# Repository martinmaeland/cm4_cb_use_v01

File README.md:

# Command Module 4 Carrierboard Utksytningsenhet
This simple pcb will be used in a deployment unit (utskytningsenhet) for controlling several drones.

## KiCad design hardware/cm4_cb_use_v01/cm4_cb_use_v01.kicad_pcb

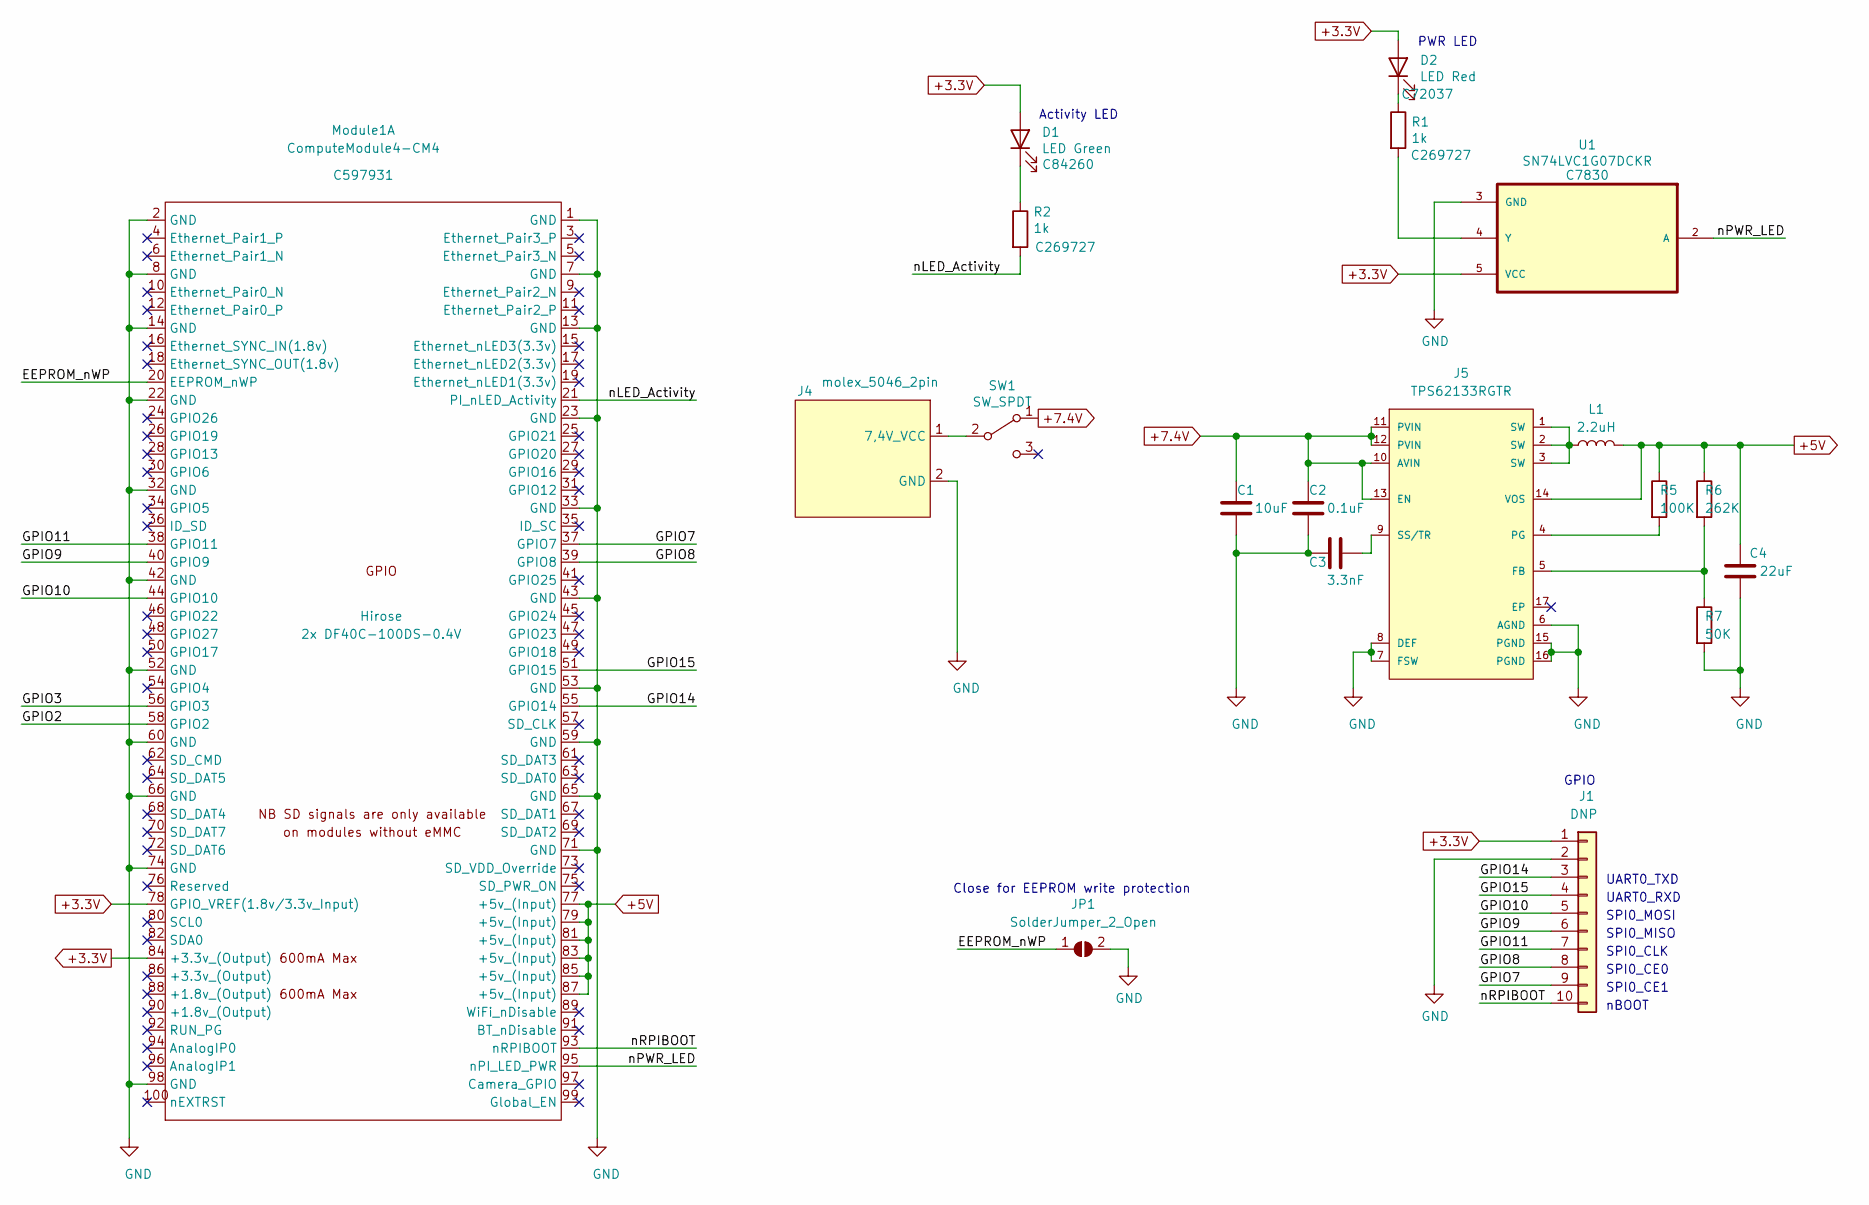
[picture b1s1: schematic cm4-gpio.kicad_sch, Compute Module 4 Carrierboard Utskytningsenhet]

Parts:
C1: 10uF; C_0805_2012Metric; MPN CL21A106KPFNNNE; LCSC PN C17024
C2: 0.1uF; C_0805_2012Metric; MPN CL21B104KBCNNNC; LCSC PN C1711
C3: 3.3nF; C_0805_2012Metric; MPN CL21B332KBANNNC; LCSC PN C53175
C4: 22uF; C_0805_2012Metric; MPN CL21C220JBANNNC; LCSC PN C1804
D1: LED Green; LED_0805_2012Metric; Part Description Green 525~537.5nm 0805 Light Emitting D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; LCSC C84260
D2: LED Red; LED_0805_2012Metric; Part Description Red 624~632nm 0805 Light Emitting Diode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; LCSC C72037
J1: DNP; PinHeader_1x10_P2.54mm_Vertical
J4: molex_5046_2pin; Molex_KK-254_AE-6410-02A_1x02_P2.54mm_Vertical
J5: TPS62133RGTR; Texas_Instruments-TPS62133RGTR-Manufacturer_Recommended; Rating Catalog
JP1: SolderJumper_2_Open; SolderJumper-2_P1.3mm_Open_RoundedPad1.0x1.5mm
L1: 2.2uH; L_0805_2012Metric; MPN SCMI201209U2R2KT; LCSC PN C479898
Module1: ComputeModule4-CM4; Raspberry-Pi-4-Compute-Module; MPN 2x DF40C-100DS-0.4V; Digi-Key_PN 2x H11615CT-ND
R1, R2: 1k; R_0805_2012Metric; MPN RMC08051K5%N; LCSC C269727
R5: 100K; R_0805_2012Metric; MPN AECR0805F100KK9; LCSC PN C328379
R6: 262K; R_0805_2012Metric
R7: 50K; R_0805_2012Metric
SW1: SW_SPDT; c&k_slide_switch_1101M2S3AQE2
U1: SN74LVC1G07DCKR; SOT65P210X110-5N; LCSC C7830

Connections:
+3.3V: D1.2 (A), D2.2 (A), J1.1, Module1.78 (GPIO_VREF(1.8v/3.3v_Input)), Module1.84 (+3.3v_(Output)), U1.5 (VCC)
+5V: C4.1, J5.14 (VOS), L1.2, Module1.77 (+5v_(Input)), Module1.79 (+5v_(Input)), Module1.81 (+5v_(Input)), Module1.83 (+5v_(Input)), Module1.85 (+5v_(Input)), Module1.87 (+5v_(Input)), R5.1, R6.1; also elsewhere on the board
+7.4V: C1.1, C2.1, J5.10 (AVIN), J5.11 (PVIN), J5.12 (PVIN), J5.13 (EN), SW1.1 (A)
/CM4 GPIO/EEPROM_nWP: JP1.1 (A), Module1.20 (EEPROM_nWP)
/CM4 GPIO/GPIO2: Module1.58 (GPIO2)
/CM4 GPIO/GPIO3: Module1.56 (GPIO3)
/CM4 GPIO/GPIO7: J1.9, Module1.37 (GPIO7)
/CM4 GPIO/GPIO8: J1.8, Module1.39 (GPIO8)
/CM4 GPIO/GPIO9: J1.6, Module1.40 (GPIO9)
/CM4 GPIO/GPIO10: J1.5, Module1.44 (GPIO10)
/CM4 GPIO/GPIO11: J1.7, Module1.38 (GPIO11)
/CM4 GPIO/GPIO14: J1.3, Module1.55 (GPIO14)
/CM4 GPIO/GPIO15: J1.4, Module1.51 (GPIO15)
/CM4 GPIO/nLED_Activity: Module1.21 (PI_nLED_Activity), R2.2
/CM4 GPIO/nPWR_LED: Module1.95 (nPI_LED_PWR), U1.2 (A)
/CM4 GPIO/nRPIBOOT: J1.10, Module1.93 (nRPIBOOT)
GND: C1.2, C2.2, C3.2, C4.2, J1.2, J4.2 (GND), J5.6 (AGND), J5.7 (FSW), J5.8 (DEF), J5.15 (PGND), J5.16 (PGND), JP1.2 (B), Module1.1 (GND), Module1.2 (GND), Module1.7 (GND), Module1.8 (GND), Module1.13 (GND), Module1.14 (GND), Module1.22 (GND), Module1.23 (GND), Module1.32 (GND), Module1.33 (GND), Module1.42 (GND), Module1.43 (GND), Module1.52 (GND), Module1.53 (GND), Module1.59 (GND), Module1.60 (GND), Module1.65 (GND), Module1.66 (GND), Module1.71 (GND), Module1.74 (GND), Module1.98 (GND), R7.2, U1.3 (GND); also elsewhere on the board
unnamed: C3.1, J5.9 (SS/TR)
unnamed: D1.1 (K), R2.1
unnamed: D2.1 (K), R1.1
unnamed: J4.1 (7,4V_VCC), SW1.2 (B)
unnamed: J5.1 (SW), J5.2 (SW), J5.3 (SW), L1.1
unnamed: J5.4 (PG), R5.2
unnamed: J5.5 (FB), R6.2, R7.1
unnamed: R1.2, U1.4 (Y)

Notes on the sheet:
Activity LED
Close for EEPROM write protection
PWR LED
GPIO
UART0_TXD
UART0_RXD
SPI0_MOSI
SPI0_MISO
SPI0_CLK
SPI0_CE0
SPI0_CE1
nBOOT

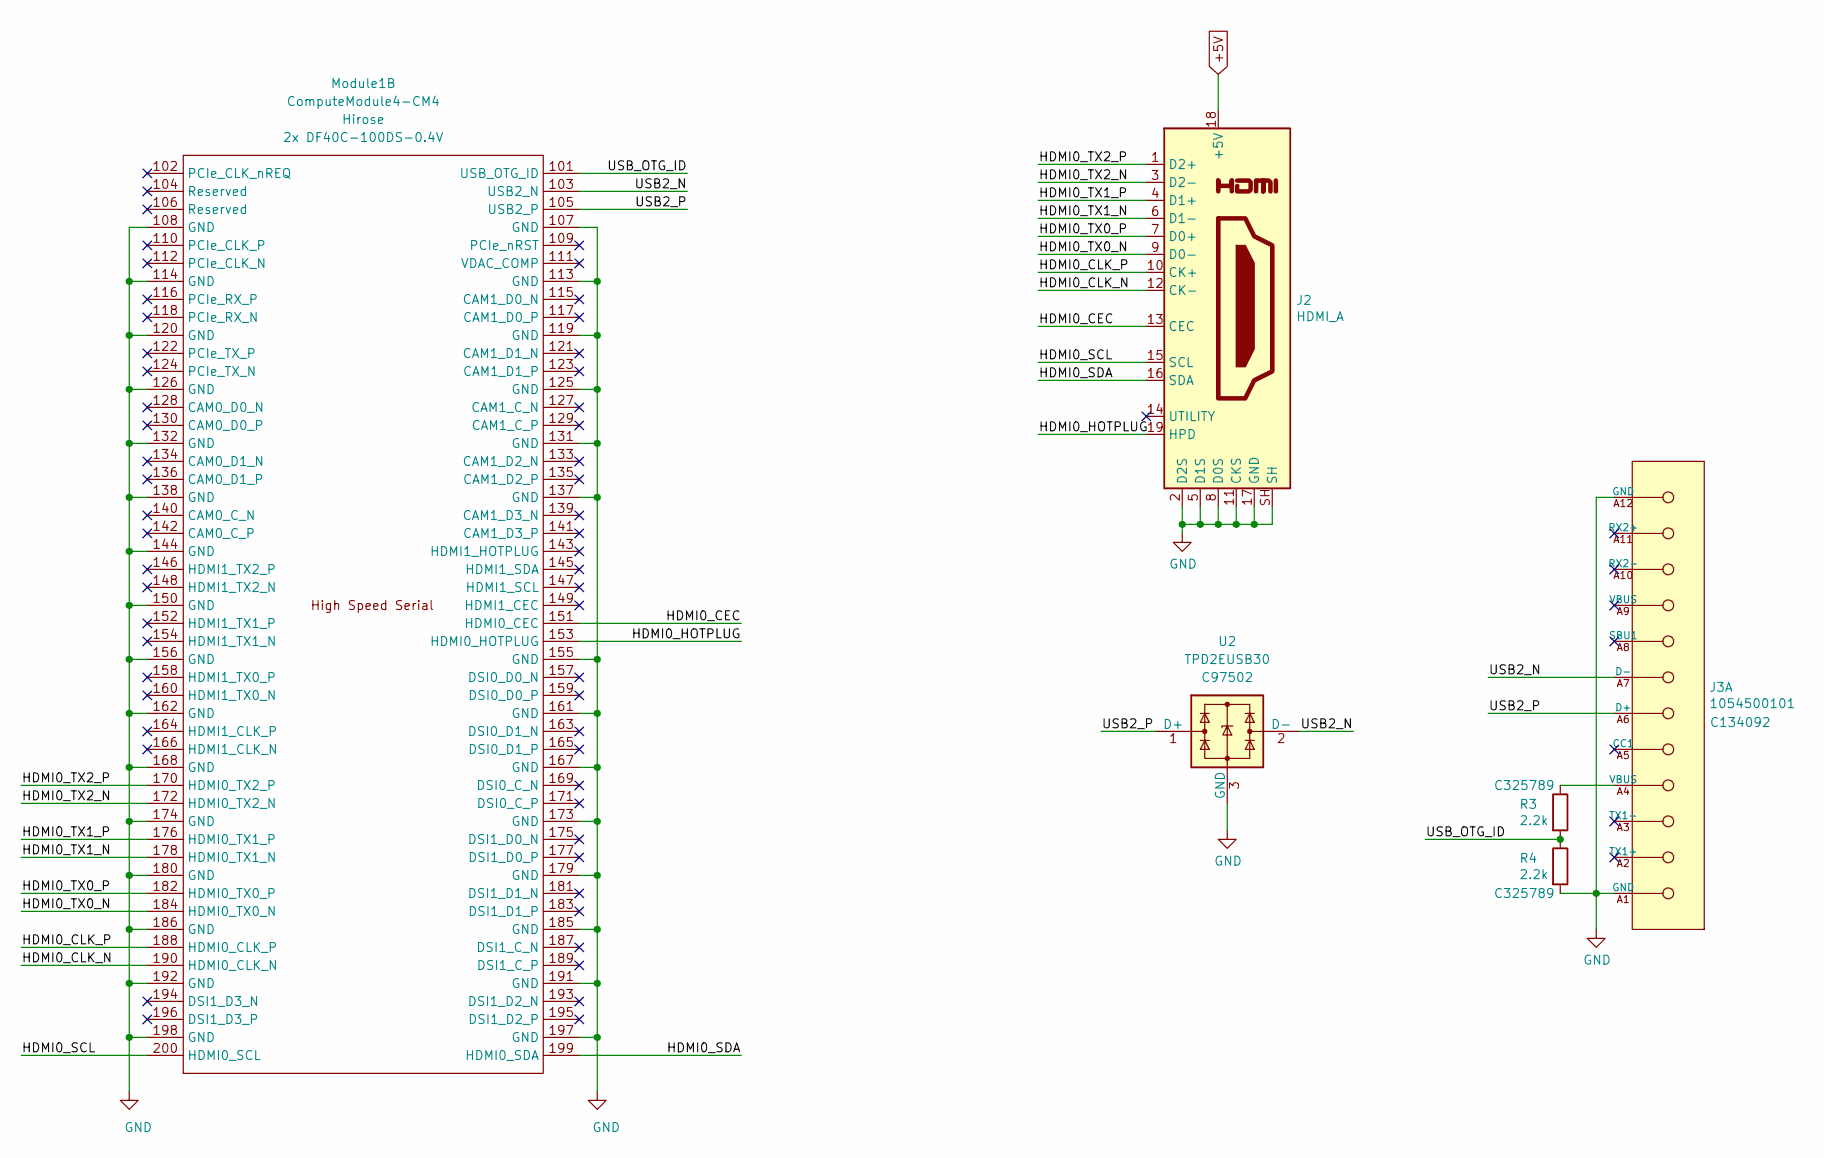
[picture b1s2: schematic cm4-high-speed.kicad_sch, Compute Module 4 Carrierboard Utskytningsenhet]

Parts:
J2: HDMI_A; molex_hdmi; LCSC C111617
J3: 1054500101; Molex-1054500101-MFG; current rating 0.25/1.25/5A; voltage rating 30V; mouser part number 538-105450-0101; digikey description CONN RCP USB3.1 TYPEC 24P SMD RA
Module1: ComputeModule4-CM4; Raspberry-Pi-4-Compute-Module; Digi-Key_PN 2x H11615CT-ND
R3, R4: 2.2k; R_0805_2012Metric; LCSC C325789
U2: TPD2EUSB30; Texas_DRT-3; MPN TPD2EUSB30DRTR; LCSC C97502

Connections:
+5V: J2.18 (+5V); also elsewhere on the board
/CM4 High Speed/HDMI0_CEC: J2.13 (CEC), Module1.151 (HDMI0_CEC)
/CM4 High Speed/HDMI0_CLK_N: J2.12 (CK-), Module1.190 (HDMI0_CLK_N)
/CM4 High Speed/HDMI0_CLK_P: J2.10 (CK+), Module1.188 (HDMI0_CLK_P)
/CM4 High Speed/HDMI0_HOTPLUG: J2.19 (HPD), Module1.153 (HDMI0_HOTPLUG)
/CM4 High Speed/HDMI0_SCL: J2.15 (SCL), Module1.200 (HDMI0_SCL)
/CM4 High Speed/HDMI0_SDA: J2.16 (SDA), Module1.199 (HDMI0_SDA)
/CM4 High Speed/HDMI0_TX0_N: J2.9 (D0-), Module1.184 (HDMI0_TX0_N)
/CM4 High Speed/HDMI0_TX0_P: J2.7 (D0+), Module1.182 (HDMI0_TX0_P)
/CM4 High Speed/HDMI0_TX1_N: J2.6 (D1-), Module1.178 (HDMI0_TX1_N)
/CM4 High Speed/HDMI0_TX1_P: J2.4 (D1+), Module1.176 (HDMI0_TX1_P)
/CM4 High Speed/HDMI0_TX2_N: J2.3 (D2-), Module1.172 (HDMI0_TX2_N)
/CM4 High Speed/HDMI0_TX2_P: J2.1 (D2+), Module1.170 (HDMI0_TX2_P)
/CM4 High Speed/USB2_N: J3.A7 (D-), Module1.103 (USB2_N), U2.2 (D-)
/CM4 High Speed/USB2_P: J3.A6 (D+), Module1.105 (USB2_P), U2.1 (D+)
/CM4 High Speed/USB_OTG_ID: Module1.101 (USB_OTG_ID), R3.2, R4.1
GND: J2.2 (D2S), J2.5 (D1S), J2.8 (D0S), J2.11 (CKS), J2.17 (GND), J2.SH, J3.A1 (GND), J3.A12 (GND), Module1.107 (GND), Module1.108 (GND), Module1.113 (GND), Module1.114 (GND), Module1.119 (GND), Module1.120 (GND), Module1.125 (GND), Module1.126 (GND), Module1.131 (GND), Module1.132 (GND), Module1.137 (GND), Module1.138 (GND), Module1.144 (GND), Module1.150 (GND), Module1.155 (GND), Module1.156 (GND), Module1.161 (GND), Module1.162 (GND), Module1.167 (GND), Module1.168 (GND), Module1.173 (GND), Module1.174 (GND), Module1.179 (GND), Module1.180 (GND), Module1.185 (GND), Module1.186 (GND), Module1.191 (GND), Module1.192 (GND), Module1.197 (GND), Module1.198 (GND), R4.2, U2.3 (GND); also elsewhere on the board
unnamed: J3.A4 (VBUS), R3.1

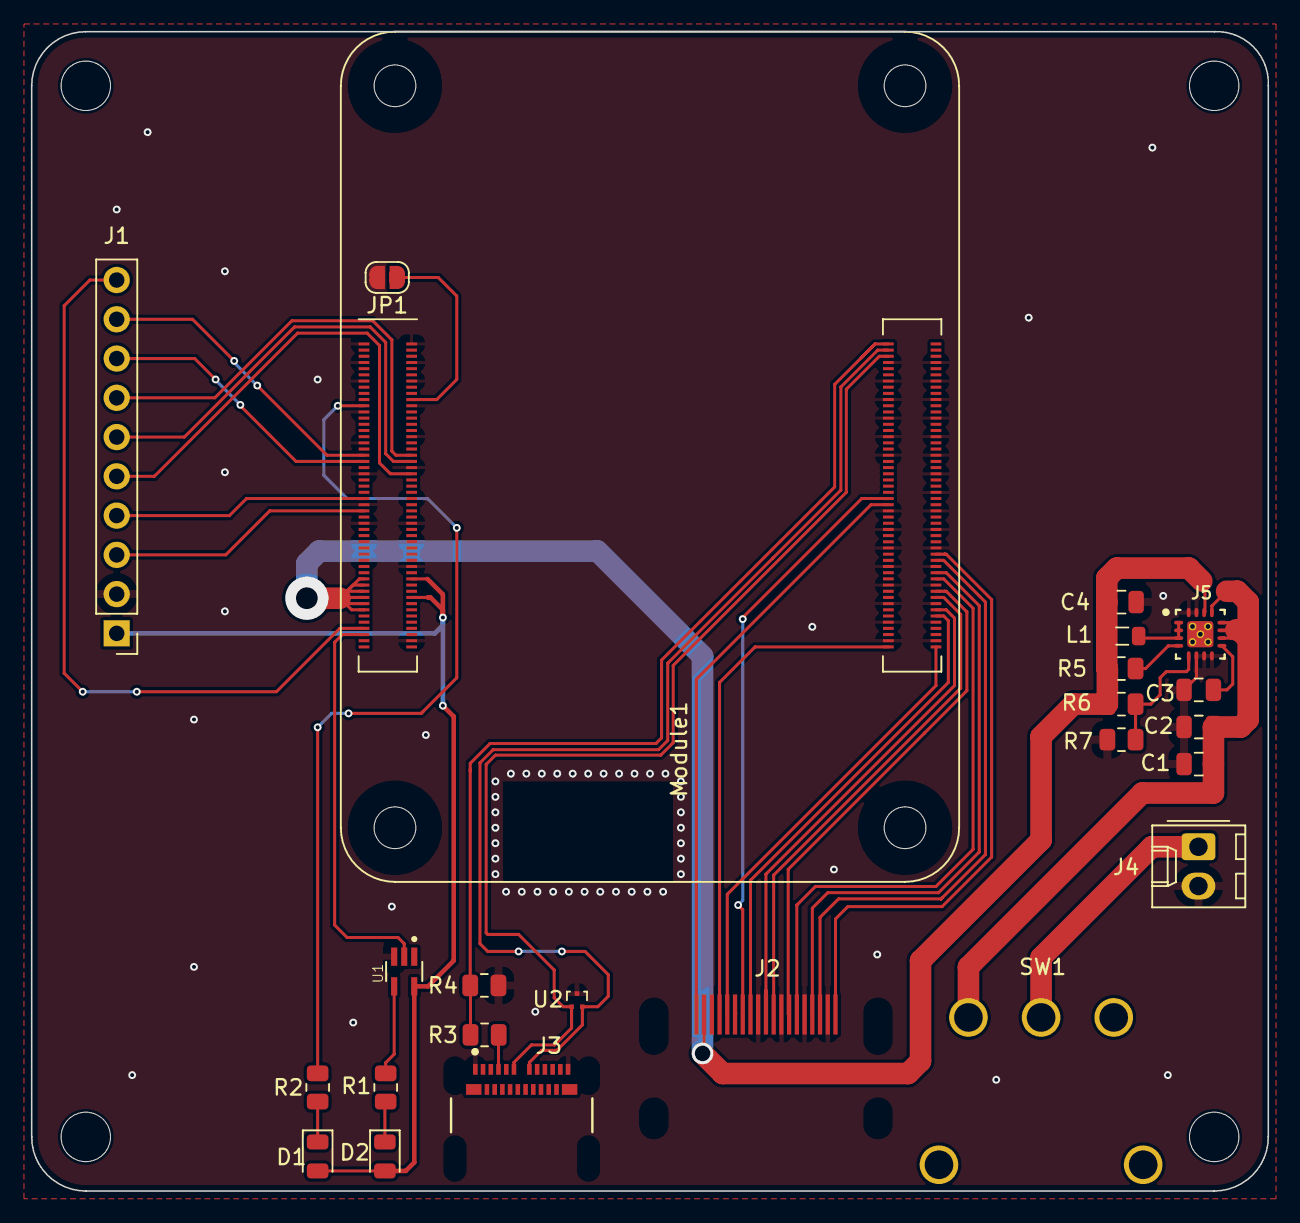
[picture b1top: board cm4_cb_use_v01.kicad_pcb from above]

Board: 2 copper layers, 80.0 x 75.0 mm, 24 parts (0 on the bottom side), 39 nets.

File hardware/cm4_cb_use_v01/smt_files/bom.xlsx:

Comment | Designator | Footprint | LCSC | Antall | Farnell | Link | Footprint ok?
10uF | C1 | Capacitor_SMD:C_0805_2012Metric | C17024 | 1 | 1867958 | https://no.farnell.com/avx/08053d106kat2a/cap-10-f-25v-10-x5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 | ja
0.1uF | C2 | Capacitor_SMD:C_0805_2012Metric | C1711 | 1 | 1833888 | https://no.farnell.com/avx/08051c104k4t2a/cap-0-1-f-100v-10-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 | ja
3.3nF | C3 | Capacitor_SMD:C_0805_2012Metric | C53175 | 1 | 1414687 | https://no.farnell.com/kemet/c0805c332k5ractu/cap-3300pf-50v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 | ja
22uF | C4 | Capacitor_SMD:C_0805_2012Metric | C1804 | 1 | 1867955 | https://no.farnell.com/avx/08056d226mat2a/cap-22-f-6-3v-20-x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 | ja
LED Green | D1 | LED_SMD:LED_0805_2012Metric | C84260 | 1 | 2748715 | https://no.farnell.com/dialight/5988181107f/led-green-300mcd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 | ja
LED Red | D2 | LED_SMD:LED_0805_2012Metric | C72037 | 1 | 2314331 | https://no.farnell.com/kingbright/kp-2012src-j4/led-0805-x-b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 | ja
HDMI_connector | J2 | MOLEX_HDMI:MOLEX_HDMI |  | 1 | 3103017 | https://no.farnell.com/molex/47151-1061/hdmi-connector-rcpt-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 | nei
USB_C | J3 | MOLEX_1054500101_usb_c:Molex-1054500101-MFG | C134092 | 1 | 2524076 | https://no.farnell.com/molex/105450-0101/usb-conn-3-1-usb-ty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 | ja
TPS62133RGTR | J5 | TPS62133:Texas_Instruments-TPS62133RGTR-Manufacturer_Recommended | C73973 | 1 | 3122975 | https://no.farnell.com/texas-instruments/tps62133rgtr/dc-dc-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 | ja
2.2uH | L1 | Inductor_SMD:L_0805_2012Metric | C479898 | 1 | 2470285 | https://no.farnell.com/murata/lqm21pn2r2mc0d/inductor-2-2uh-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 | ja
Hirose_connector | Module1 | HRS:HRS_connector | C597931 | 2 | 2427679 | https://no.farnell.com/hirose-hrs/df40c-100ds-0-4v-51/connec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 | ja
1k | R1,R2 | Resistor_SMD:R_0805_2012Metric | C269727 | 2 | 1469847 | https://no.farnell.com/vishay/crcw08051k00fkea/res-1k-1-0-12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 | ja
2.2k | R3,R4 | Resistor_SMD:R_0805_2012Metric | C325789 | 2 | 1577663 | https://no.farnell.com/panasonic/era6aeb222v/res-2k2-0-1-0-1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 | ja
100K | R5 | Resistor_SMD:R_0805_2012Metric | C328379 | 1 | 1469860 | https://no.farnell.com/vishay/crcw0805100kfkea/res-100k-1-0-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 | ja
SN74LVC1G07DCKR | U1 | SN74LVC1G07DCKR:SOT65P210X110-5N | C7830 | 1 | 3119597 | https://no.farnell.com/texas-instruments/sn74lvc1g07dckr/buf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 | ja
TPD2EUSB30 | U2 | Package_TO_SOT_SMD:Texas_DRT-3 | C97502 | 1 | 3116502 | https://no.farnell.com/search?st=tpd2eusb30 | ja

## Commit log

2021-03-05 New repo
2021-03-05 added usb-c and hdmi
2021-03-06 added some 3d models
2021-03-07 added 3d models and started pcb layout
2021-03-09 First draft done
2021-03-16 Finished v01
2021-03-31 made some mechanical drawings
2021-05-04 minor changes and added image

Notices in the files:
hardware/cm4_cb_use_v01/cm4-gpio.kicad_sch:
creativecommons.org/licenses/by-sa/4.0
License: CC BY-SA 4.0
hardware/cm4_cb_use_v01/cm4_cb_use_v01.kicad_pcb:
creativecommons.org/licenses/by/4.0
